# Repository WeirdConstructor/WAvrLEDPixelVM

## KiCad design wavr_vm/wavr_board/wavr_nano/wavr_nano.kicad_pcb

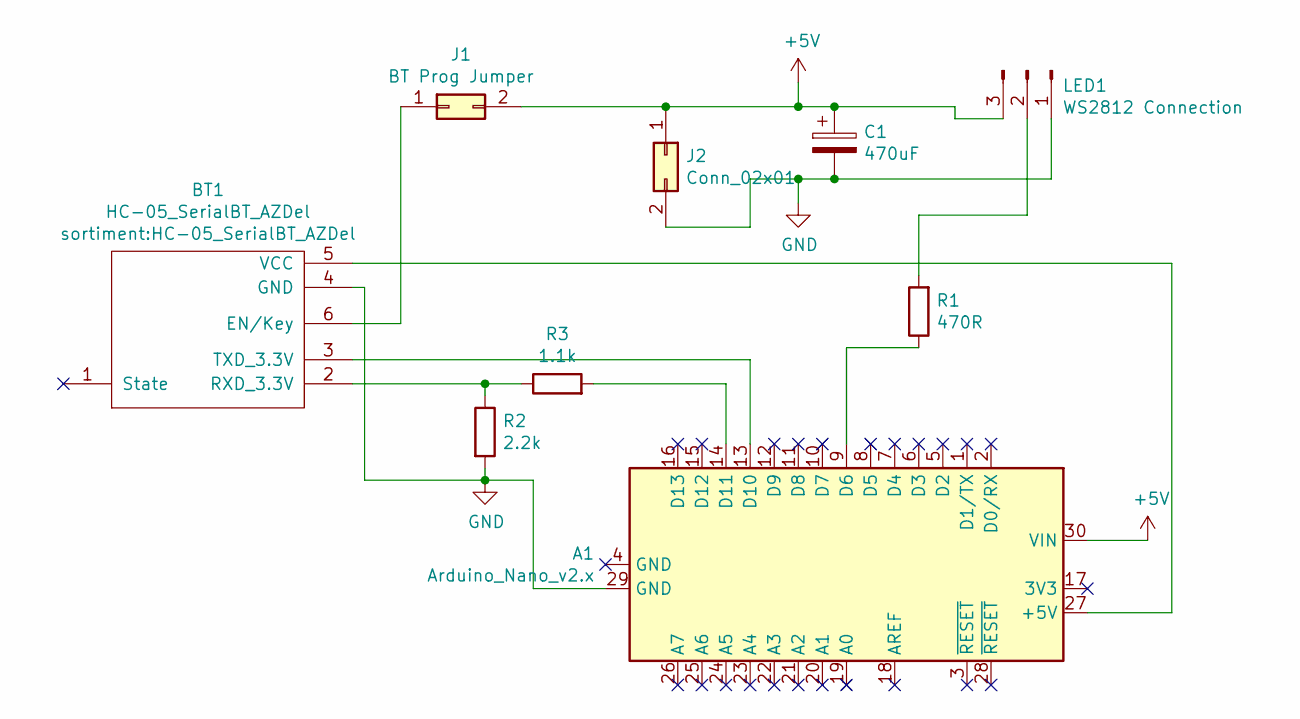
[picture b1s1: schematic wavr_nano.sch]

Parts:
A1: Arduino_Nano_v2.x; Arduino_Nano
BT1: HC-05_SerialBT_AZDel
C1: 470uF; CP_Radial_D10.0mm_P5.00mm
J1: BT Prog Jumper; PinHeader_1x02_P2.54mm_Vertical
J2: Conn_02x01; PinHeader_1x02_P2.54mm_Vertical
LED1: WS2812 Connection; PinHeader_1x03_P2.54mm_Horizontal
R1: 470R; R_Axial_DIN0207_L6.3mm_D2.5mm_P10.16mm_Horizontal
R2: 2.2k; R_Axial_DIN0207_L6.3mm_D2.5mm_P10.16mm_Horizontal
R3: 1.1k; R_Axial_DIN0207_L6.3mm_D2.5mm_P10.16mm_Horizontal

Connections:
+5V: A1.30 (VIN), C1.1, J1.2, J2.1, LED1.3
GND: A1.29 (GND), BT1.4 (GND), C1.2, J2.2, LED1.1, R2.2
unnamed: A1.9 (D6), R1.1
unnamed: A1.13 (D10), BT1.3 (TXD_3.3V)
unnamed: A1.14 (D11), R3.2
unnamed: A1.27 (+5V), BT1.5 (VCC)
unnamed: BT1.2 (RXD_3.3V), R2.1, R3.1
unnamed: BT1.6 (EN/Key), J1.1
unnamed: LED1.2, R1.2

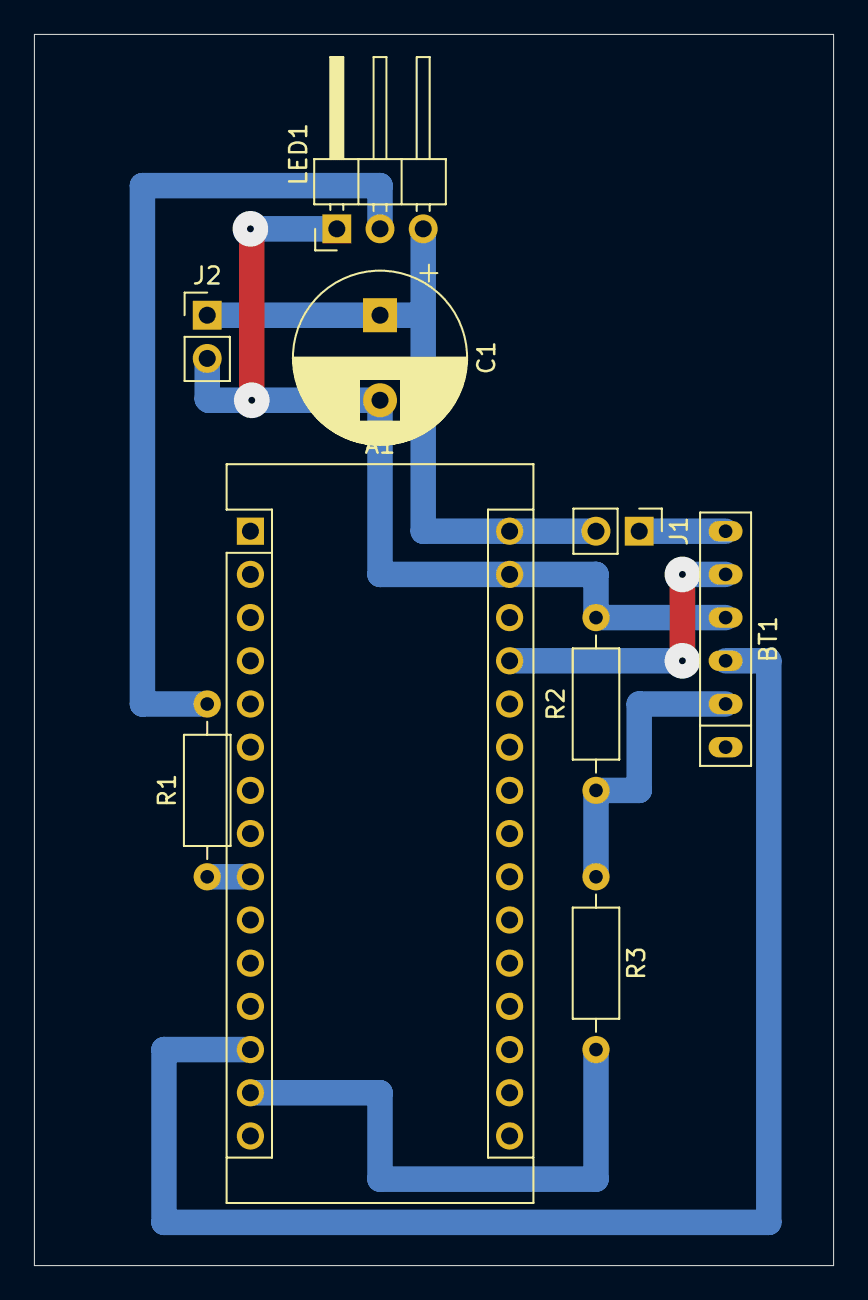
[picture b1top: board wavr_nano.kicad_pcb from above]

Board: 2 copper layers, 47.0 x 72.4 mm, 9 parts (0 on the bottom side), 9 nets.

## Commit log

2021-04-17 initial commit of basic working sketch
2021-04-17 added VM
2021-04-17 implemented more ops for the vm
2021-04-18 added handshake for serial communication
2021-04-18 added imap, fmap and rand
2021-04-19 implemented and tested software serial
2021-05-02 added proper makefile to get rid of the arduino IDE
2021-05-02 added schematics
2021-05-09 just documentation and fixed OP_FMAP
2021-05-10 implemented op parsing and added serial communication command line tool
2021-05-16 reduced program memory in favor of up to 248 controllable LEDs
2021-05-16 checked memory with freeMemory
